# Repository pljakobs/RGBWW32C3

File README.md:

# RGBWW32C3
## a new, smaller RGBWW controller built around the ESP32C3M0 module

This is based on the original design by Patrick Jahns but modified to fit into a much smaller footprint and use the much more capable ESP32 Platform - in this case the C3 Wroom 02 module.

The ESP32C3 is a risc-v based implementation of the ESP32 µC family, providing much the same peripherals as the xtensa based chips, but at a much lower price point.

The design is straight forward:

According to the [ESP32C3Wroom02 Datasheet](https://www.espressif.com/sites/default/files/documentation/esp32-c3-wroom-02_datasheet_en.pdf) the strapping pins are
|Pin|Default|SPI Boot (normal)|Download Boot (prg)|
|:--|:------|:---------------:|:-----------------:|
|IO2|N/A|HIGH|HIGH|
|IO8|N/A|ignore|HIGH|
|IO9|weak pullup|HIGH|LOW|

Therefore, IO2 and IO8 need to be pulled high, IO9 should be pulled high for normal operation and pulled to GND for programming / Booting.

That results in the following strapping / switching schematic:

The output stage has, from a schematic point of view, mostly remained unchanged (as if there was a lot to change on driving N-Channel MOSFETS). The actual MOSFETs however have been replaced with much smaller packaged types. Currently, I'm looking at Alpha&Omega devices AO4808 or better (there are some in the family that go up to 11.5A Drain current per channel and 30V VDS which would make the mini a fully featured replacement for the original controller, although the TO92 IRFZ44N theoretically could drive 49A of drain source current, but the design was never built to provide that).

One of the biggest changes from the original design by Patrick and the last Version (green boards) was that I ditched the 3rd party DC/DC modules in favour of a power converter on board, designed with [TI Power Designer Webbench](https://webench.ti.com/power-designer/switching-regulator?powerSupply=0), a tool that I have come to value a lot. 
This time, the requirement was to make the power converter smaller but no less powerful (still capable of pushing up to 600mA at 3.3V but optimized for 200mA)

The last bit of the schematic is to programming port. This device will not be easily programmed "at home" as it should, normally, come without a header installed (which just now makes me think why I have a PRG button on it after all, I should remove that). The programming port is six pads on the bottom of the board, fit to mount a 1/20" SMD pin header that matches the six pin cable of the [esp_prog](https://docs.espressif.com/projects/espressif-esp-iot-solution/en/latest/hw-reference/ESP-Prog_guide.html). The intention is to have a printed jig where the boards can be initially programmed, everything after that should be done OTA

The routed board in Eagle 7.7 (yes, I'm still using it when things need to go fast) now looks like this:

Lastly, here are the board images as generated by the Aisler board inspector:

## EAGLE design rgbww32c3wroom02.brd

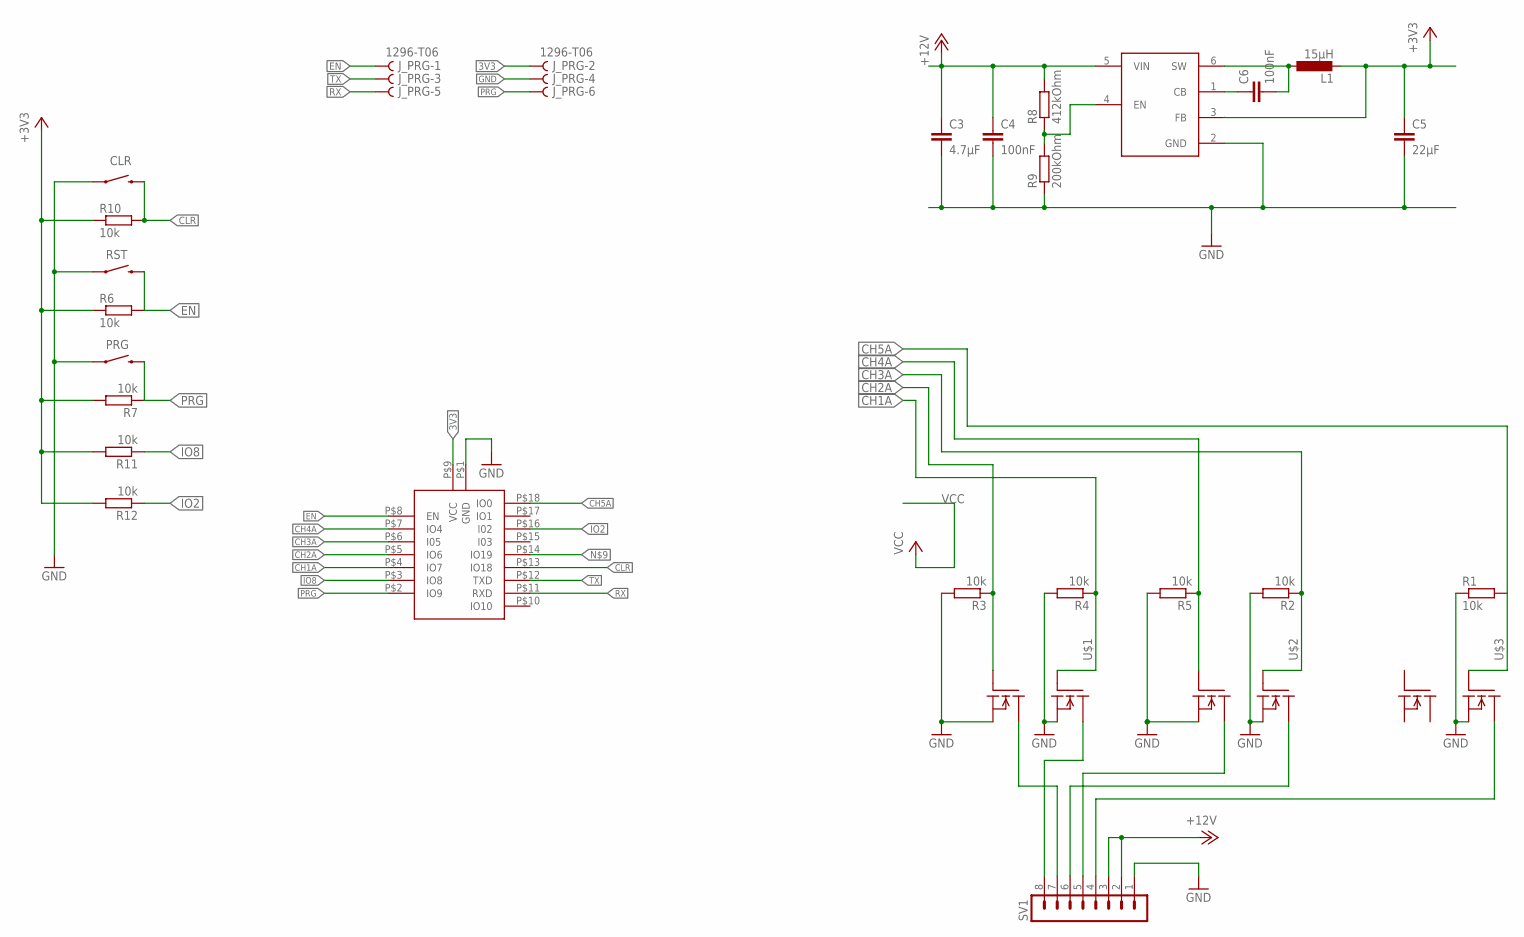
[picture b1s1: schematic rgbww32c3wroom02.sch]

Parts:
C3: 4.7µF; C1210
C4, C6: 100nF; C0805
C5: 22µF; C0805
CLR: SWITCH-MOMENTARY-2SMD-1101NE; TACTILE-SWITCH-1101NE
J_PRG: 1296-T06; 06
L1: 15µH; LPS4018
PRG: SWITCH-MOMENTARY-2SMD-1101NE; TACTILE-SWITCH-1101NE
R1, R2, R3, R4, R5, R6, R7, R10, R11, R12: 10k; R0805
R8: 412kOhm; M0805
R9: 200kOhm; M0805
RST: SWITCH-MOMENTARY-2SMD-1101NE; TACTILE-SWITCH-1101NE
SV1: MA08-1
U$1, U$2, U$3: AOD4806; SO08
U$5: ESP32C3WROOM02; SMD
U$6: TPS5604030; SOT23-6

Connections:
3V3: C5.1, J_PRG.2, L1.2, R6.1, R7.2, R10.1, R11.2, R12.2, U$5.P$9 (VCC), U$6.3 (FB)
12V: C3.1, C4.1, R8.2, SV1.2, SV1.3, U$6.5 (VIN)
BOOT: C6.1, U$6.1 (CB)
CH1: SV1.8, U$1.5 (D), U$1.6 (D)
CH1A: R4.1, U$1.4 (G), U$5.P$4 (IO7)
CH2: SV1.7, U$1.7 (D1), U$1.8 (D1)
CH2A: R3.1, U$1.2 (G1), U$5.P$5 (IO6)
CH3: SV1.6, U$2.5 (D), U$2.6 (D)
CH3A: R2.1, U$2.4 (G), U$5.P$6 (I05)
CH4: SV1.5, U$2.7 (D1), U$2.8 (D1)
CH4A: R5.1, U$2.2 (G1), U$5.P$7 (IO4)
CH5: SV1.4, U$3.5 (D), U$3.6 (D)
CH5A: R1.2, U$3.4 (G), U$5.P$18 (IO0)
CLR: CLR.2, R10.2, U$5.P$13 (IO18)
EN: J_PRG.1, R6.2, RST.2, U$5.P$8 (EN)
EN_P: R8.1, R9.2, U$6.4 (EN)
GND: C3.2, C4.2, C5.2, CLR.1, J_PRG.4, PRG.1, R1.1, R2.2, R3.2, R4.2, R5.2, R9.1, RST.1, SV1.1, U$1.1 (S1), U$1.3 (S), U$2.1 (S1), U$2.3 (S), U$3.3 (S), U$5.P$1 (GND), U$6.2 (GND)
IO2: R12.1, U$5.P$16 (I02)
IO8: R11.1, U$5.P$3 (IO8)
PRG: J_PRG.6, PRG.2, R7.1, U$5.P$2 (IO9)
RX: J_PRG.5, U$5.P$11 (RXD)
SW: C6.2, L1.1, U$6.6 (SW)
TX: J_PRG.3, U$5.P$12 (TXD)

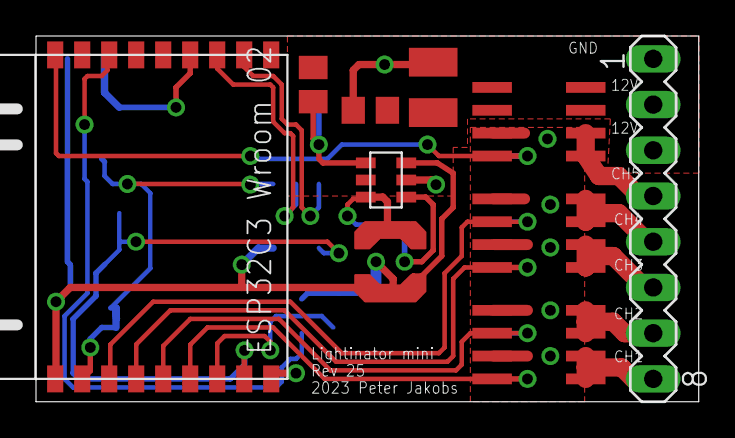
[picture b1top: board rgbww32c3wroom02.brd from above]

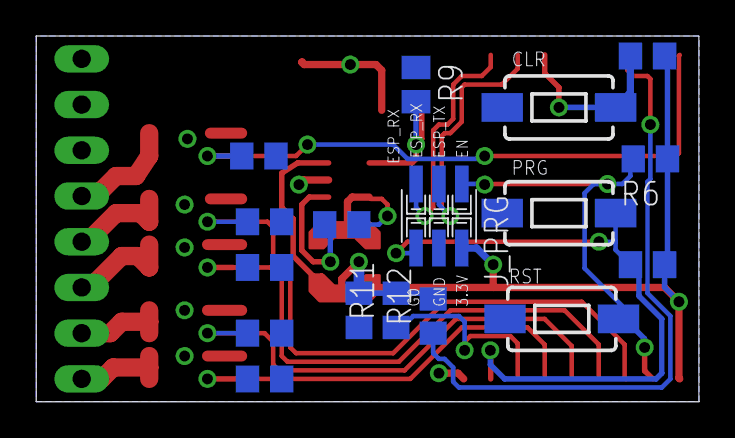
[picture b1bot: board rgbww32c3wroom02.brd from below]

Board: 2 copper layers, 36.8 x 20.3 mm, 27 parts (17 on the bottom side), 23 nets.

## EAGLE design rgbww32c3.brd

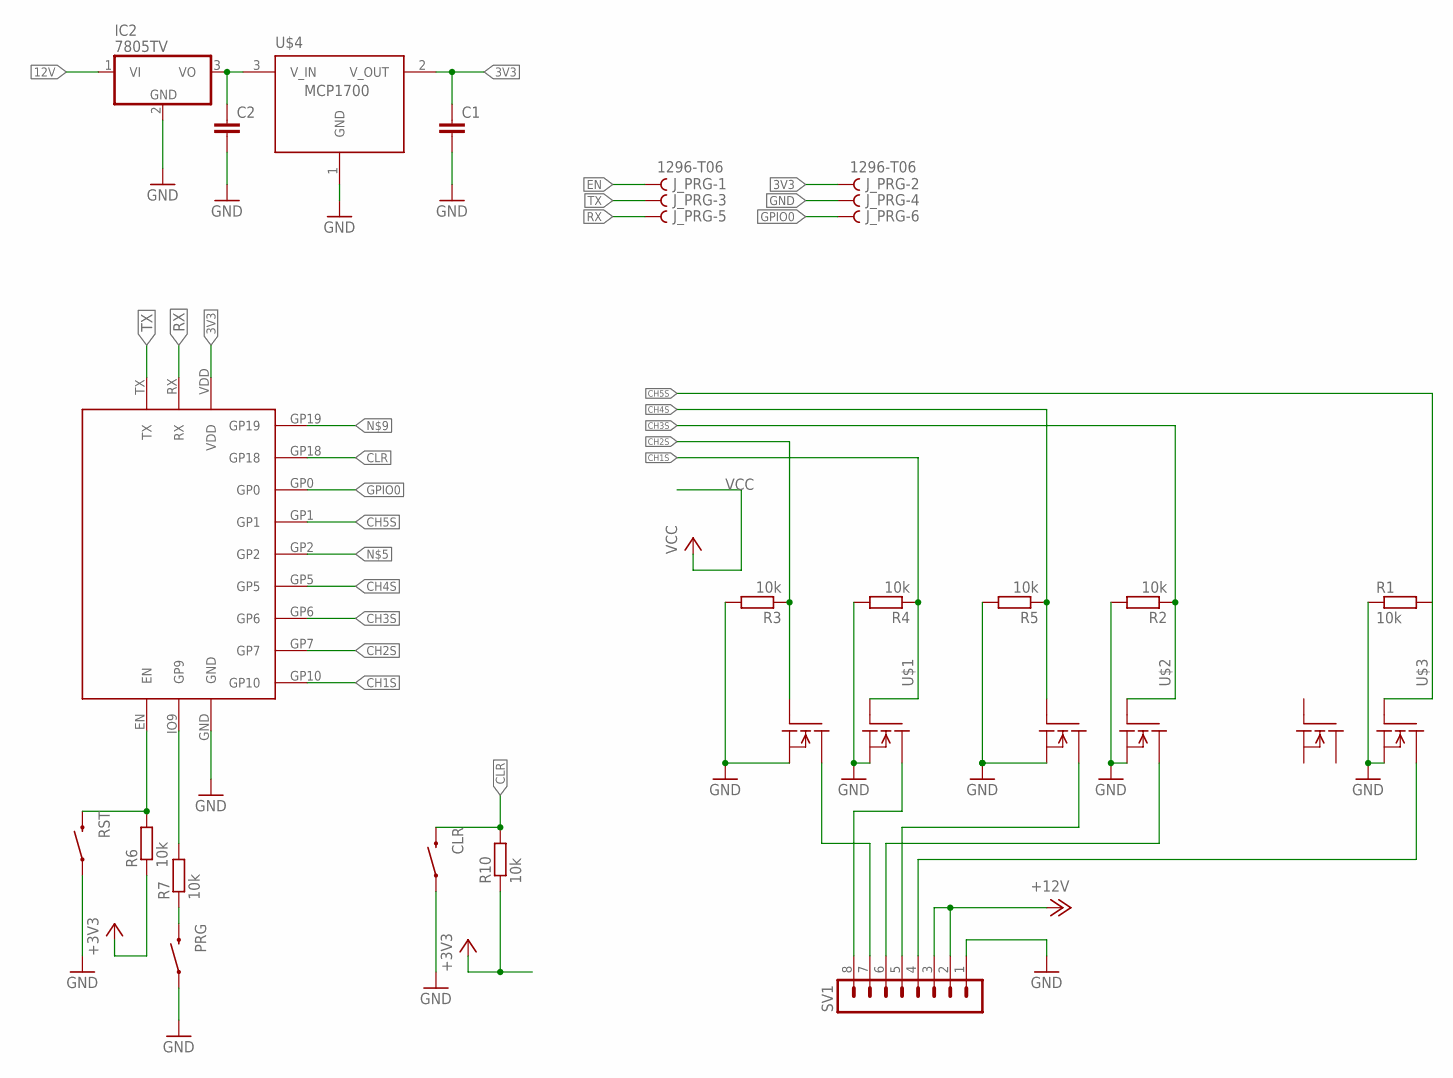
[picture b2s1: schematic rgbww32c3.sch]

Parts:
C1, C2: C-EUC1206; C1206
CLR: SWITCH-MOMENTARY-2SMD-1101NE; TACTILE-SWITCH-1101NE
IC2: 7805TV; TO220V
J_PRG: 1296-T06; 06
PRG: SWITCH-MOMENTARY-2SMD-1101NE; TACTILE-SWITCH-1101NE
R1, R2, R3, R4, R5, R6, R7, R10: 10k; R0805
RST: SWITCH-MOMENTARY-2SMD-1101NE; TACTILE-SWITCH-1101NE
SV1: MA08-1
U$1, U$2, U$3: AOD4806; SO08
U$4: MCP1700; SOT-23
U$5: ESP32-C3M_FLAT; LAY_FLAT

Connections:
3V3: C1.1, J_PRG.2, R6.1, R10.1, U$4.2 (V_OUT), U$5.VDD
5V: C2.1, IC2.3 (VO), U$4.3 (V_IN)
12V: IC2.1 (VI), SV1.2, SV1.3
CH1: SV1.8, U$1.5 (D), U$1.6 (D)
CH1S: R4.1, U$1.4 (G), U$5.GP10
CH2: SV1.7, U$1.7 (D1), U$1.8 (D1)
CH2S: R3.1, U$1.2 (G1), U$5.GP7
CH3: SV1.6, U$2.5 (D), U$2.6 (D)
CH3S: R2.1, U$2.4 (G), U$5.GP6
CH4: SV1.5, U$2.7 (D1), U$2.8 (D1)
CH4S: R5.1, U$2.2 (G1), U$5.GP5
CH5: SV1.4, U$3.5 (D), U$3.6 (D)
CH5S: R1.2, U$3.4 (G), U$5.GP1
CLR: CLR.2, R10.2, U$5.GP18
EN: J_PRG.1, R6.2, RST.2, U$5.EN
GND: C1.2, C2.2, CLR.1, IC2.2 (GND), J_PRG.4, PRG.1, R1.1, R2.2, R3.2, R4.2, R5.2, RST.1, SV1.1, U$1.1 (S1), U$1.3 (S), U$2.1 (S1), U$2.3 (S), U$3.3 (S), U$4.1 (GND), U$5.GND
GPIO0: J_PRG.6, U$5.GP0
unnamed: R7.2, U$5.IO9 (GP9)
unnamed: PRG.2, R7.1
RX: J_PRG.5, U$5.RX
TX: J_PRG.3, U$5.TX

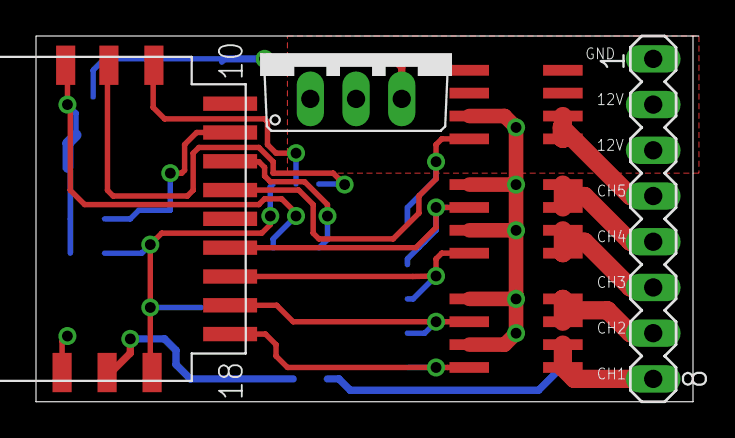
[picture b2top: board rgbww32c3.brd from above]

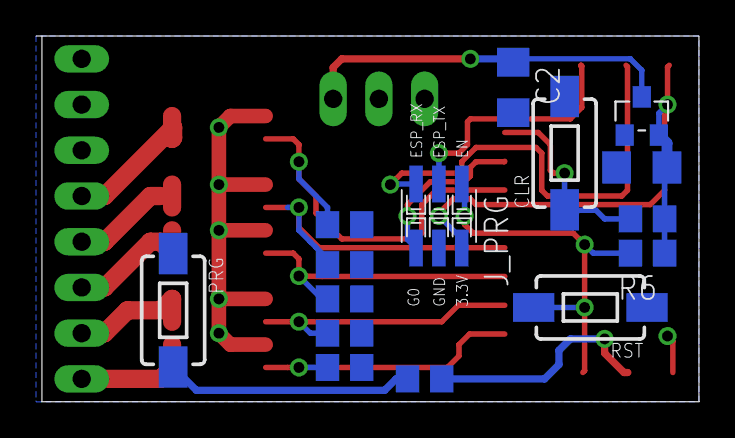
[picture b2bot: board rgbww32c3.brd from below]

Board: 2 copper layers, 36.8 x 20.3 mm, 21 parts (15 on the bottom side), 21 nets.

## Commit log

2022-10-22 adjusted channel names
2022-11-07 initial testing version
    programming the ESP32 now works using an esp_prog. It does require to pull GPIO9 low, hence the extra PRG button. The auto programming function of other ESP models (GPIO0) does not work on the C3, it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
2022-11-07 had the 12V->5V converter backwards
2022-11-07 minor routing error
2022-11-07 few routing corrections to better avoid short circuits
2023-09-06 new layout for wroom02 module
    reworked the layout to use the ESP Wroom 02 module which should be easier to solder and route
2023-09-06 moved the 3.3V reg to clean up things a bit. Not sure if it will be in the way of the 5V VRs inductance
2023-09-06 some corrections before production
2023-10-30 built local voltage reg
2023-10-30 added local switching voltage regulator
2023-10-30 resolved two minor mistakes
    The footprint for L1 still needs to get it's solder mask taken off.
2023-10-30 updated solder mask retraction
2023-10-31 added gerber pictures
2023-10-31 small changes on the 12V side
    moved the input caps so that the 12V pins are now oriented towards the switching controller. nothing major but might get a wee bit better filtering due to smaller loop area
2023-11-07 added scematic images
2023-11-07 removed confusing old boards
2023-11-07 updated board
2023-11-11 corrected PRG pin for esp32c3
    sometimes, I notice things way late. Like the fact that the PRG pin on the esp32c3 is no longer GPIO0 as it was with all xtensa based chips but now it's GPIO9.
    I was using GPIO9 as an output pin with a 10k pulldown which should have always set the chip into download mode - not what I wanted. I have now shuffeled pins around and this should be ok now.
2023-11-11 fixed a minor routing error
    after viewing the result on aisler.net, I noticed that I had doubled up a via (the same via twice in the same location). Fixed that.
2023-11-11 updated board shot
2023-11-11 updated the board images as generated by Aisler

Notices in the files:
parts and their libraries:
SparkFun-Electromechanical: Licensing: Creative Commons ShareAlike 4.0 International - https://creativecommons.org/licenses/by-sa/4.0
SparkFun-Aesthetics: Licensing: CC v3.0 Share-Alike You are welcome to use this library for commercial purposes.
